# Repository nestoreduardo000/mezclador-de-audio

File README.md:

El objetivo de este proyecto es diseñar una placa de circuito impreso (PCB) para construir una mezcladora de audio estéreo básica.

El equipo dispondrá de dos entradas de audio: una entrada de línea estéreo y una entrada para micrófono, cuya ganancia podrá ajustarse de forma independiente.

La salida proporcionará la mezcla de ambas fuentes de audio, conservando la señal en formato estéreo..

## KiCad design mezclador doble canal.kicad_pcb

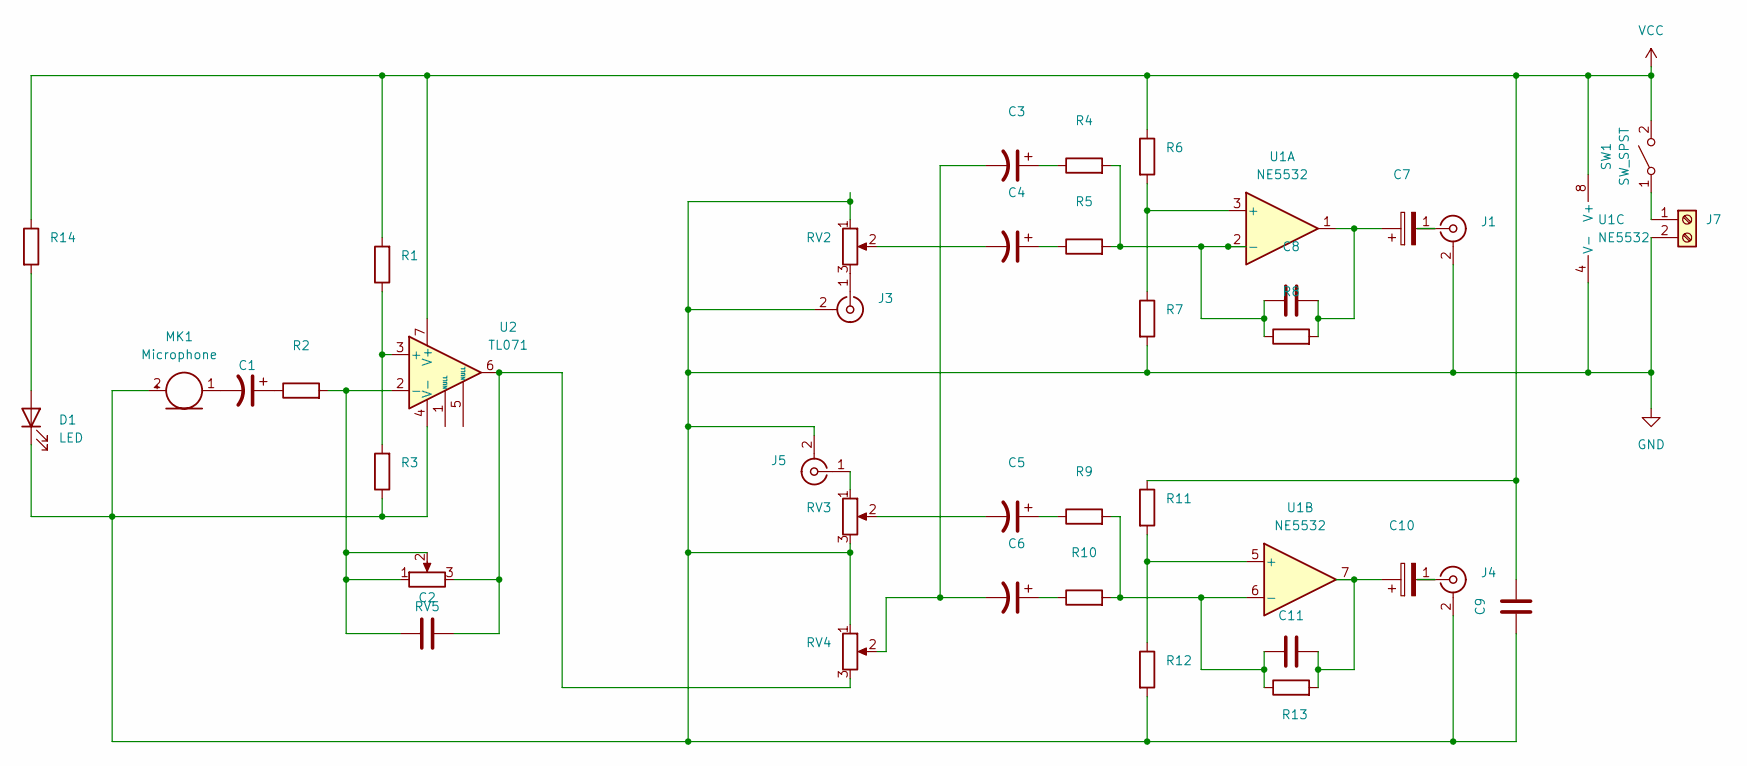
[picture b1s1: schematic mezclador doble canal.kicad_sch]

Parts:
C1: C_Polarized_US; C_Disc_D5.0mm_W2.5mm_P5.00mm
C2, C8, C9, C11: C; C_Disc_D5.0mm_W2.5mm_P5.00mm
C3, C4, C5, C6: C_Polarized_US; CP_Radial_D5.0mm_P2.50mm
C7, C10: C_Polarized; CP_Radial_D5.0mm_P2.50mm
D1: LED; double wire
J1, J3, J4, J5: Conn_Coaxial; double wire
J7: Screw_Terminal_01x02; double wire
MK1: Microphone; double wire
R1, R2, R3, R4, R5, R6, R7, R8, R9, R10, R11, R12, R13: R; R_Axial_DIN0207_L6.3mm_D2.5mm_P10.16mm_Horizontal
R14: R; R_Axial_DIN0207_L6.3mm_D2.5mm_P7.62mm_Horizontal
RV2, RV3, RV4, RV5: R_Potentiometer; potentiometer pads
SW1: SW_SPST; double wire
U1: NE5532; DIP-8_W7.62mm
U2: TL071; DIP-8_W7.62mm

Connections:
GND: C9.1, D1.1 (K), J1.2 (Ext), J3.2 (Ext), J4.2 (Ext), J5.2 (Ext), J7.2, MK1.2 (+), R3.1, R7.2, R12.2, RV2.1, RV3.3, RV4.1, U1.4 (V-), U2.4 (V-)
unnamed: C1.1, R2.1
unnamed: C2.2, RV4.3, RV5.3, U2.6
unnamed: C3.1, R4.1
unnamed: C3.2, C6.2, RV4.2
unnamed: C4.1, R5.1
unnamed: C4.2, RV2.2
unnamed: C5.1, R9.1
unnamed: C5.2, RV3.2
unnamed: C6.1, R10.1
unnamed: C7.1, C8.2, R8.2, U1.1
unnamed: C10.1, C11.2, R13.2, U1.7
unnamed: D1.2 (A), R14.2
unnamed: C7.2, J1.1 (In)
unnamed: J3.1 (In), RV2.3
unnamed: C10.2, J4.1 (In)
unnamed: J5.1 (In), RV3.1
unnamed: J7.1, SW1.1 (A)
unnamed: C1.2, MK1.1 (-)
unnamed: R6.2, R7.1, U1.3 (+)
unnamed: C8.1, R4.2, R5.2, R8.1, U1.2 (-)
unnamed: R11.2, R12.1, U1.5 (+)
unnamed: C11.1, R9.2, R10.2, R13.1, U1.6 (-)
unnamed: R1.1, R3.2, U2.3 (+)
unnamed: C2.1, R2.2, RV5.1, RV5.2, U2.2 (-)
VCC: C9.2, R1.2, R6.1, R11.1, R14.1, SW1.2 (B), U1.8 (V+), U2.7 (V+)

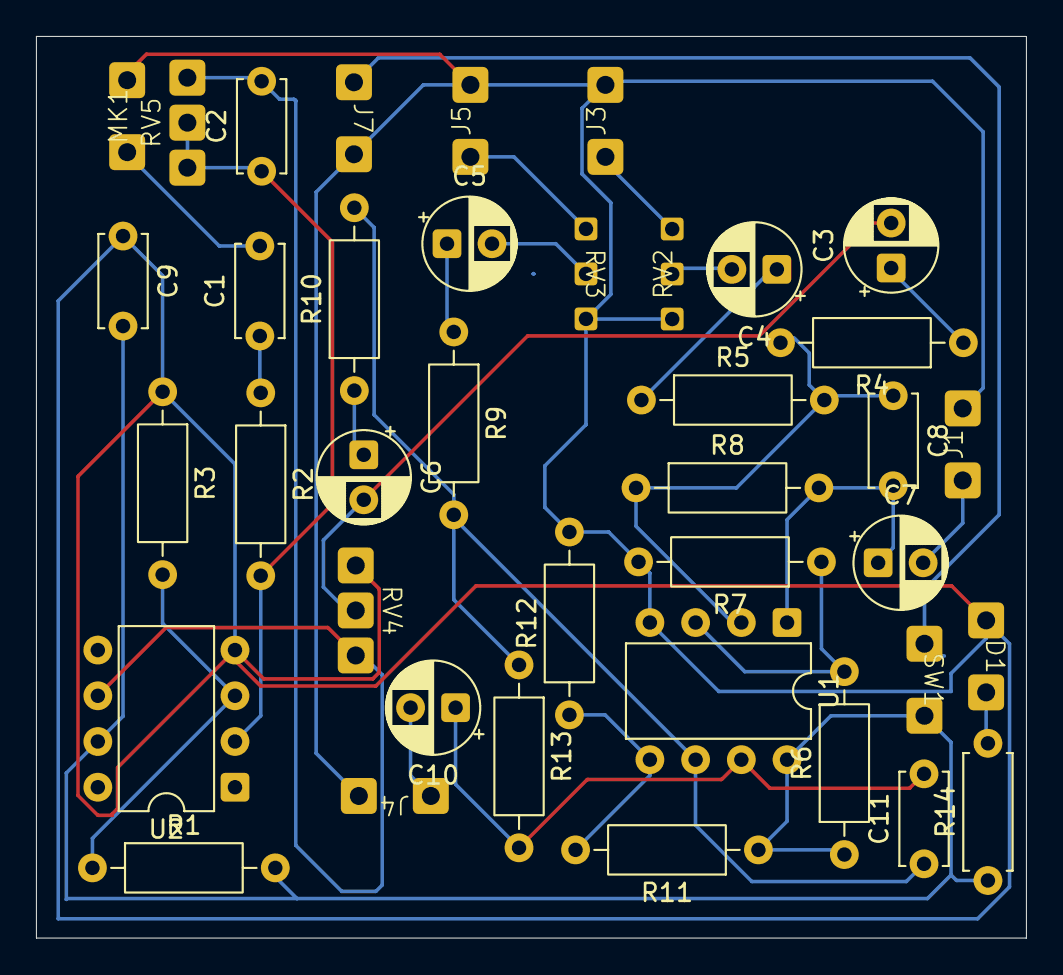
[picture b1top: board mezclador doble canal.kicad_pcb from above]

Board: 2 copper layers, 55.0 x 50.1 mm, 39 parts (0 on the bottom side), 26 nets.
